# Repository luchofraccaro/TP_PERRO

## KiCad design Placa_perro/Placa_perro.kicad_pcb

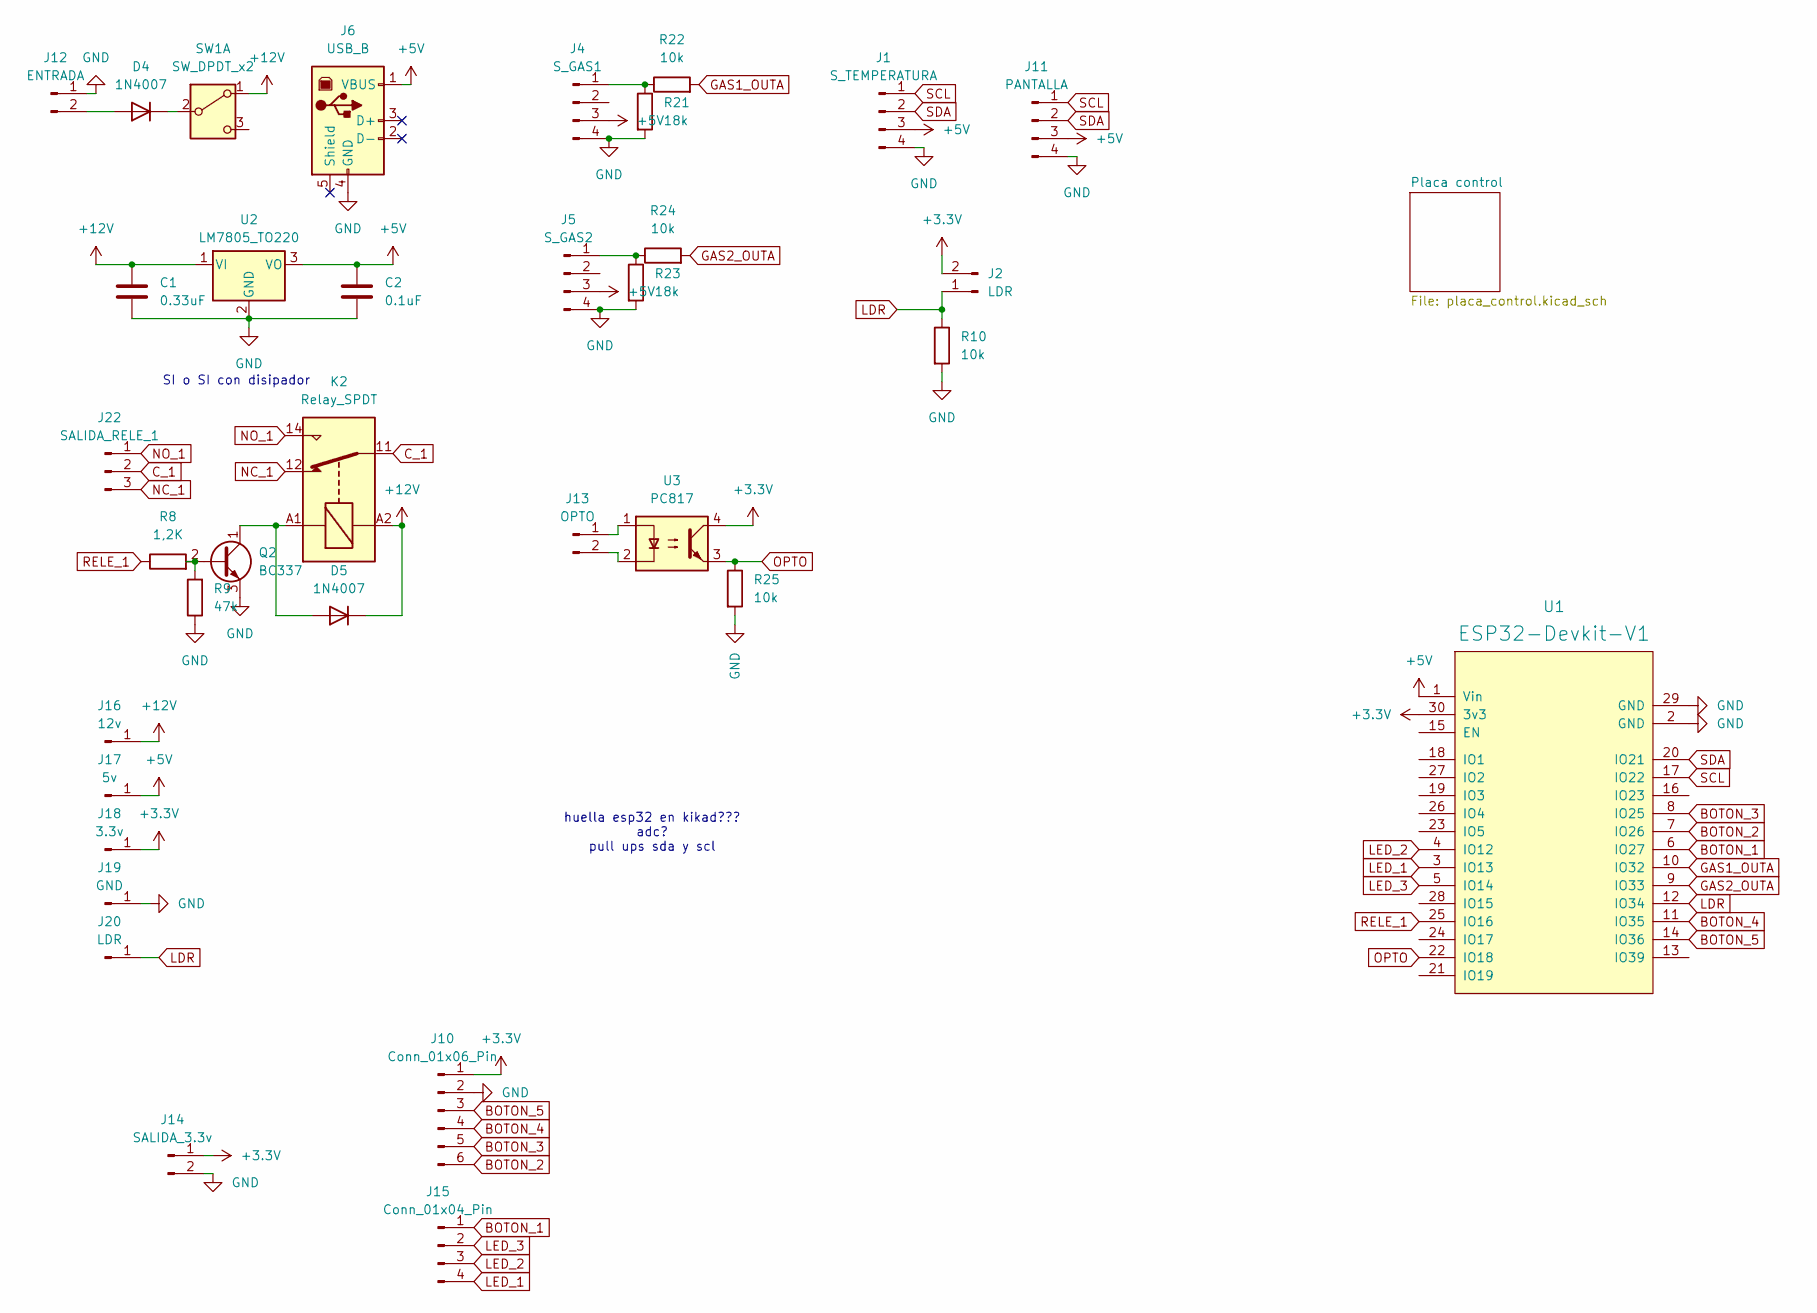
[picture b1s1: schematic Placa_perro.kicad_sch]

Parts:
C1: 0.33uF; C_Disc_D3.8mm_W2.6mm_P2.50mm
C2: 0.1uF; C_Disc_D3.8mm_W2.6mm_P2.50mm
D4, D5: 1N4007; D_DO-41_SOD81_P10.16mm_Horizontal
J1: S_TEMPERATURA; Molex_KK-254_AE-6410-04A_1x04_P2.54mm_Vertical
J2: LDR; Molex_KK-254_AE-6410-02A_1x02_P2.54mm_Vertical
J4: S_GAS1; Molex_KK-254_AE-6410-04A_1x04_P2.54mm_Vertical
J5: S_GAS2; Molex_KK-254_AE-6410-04A_1x04_P2.54mm_Vertical
J6: USB_B; USB_B_Lumberg_2411_02_Horizontal
J10: Conn_01x06_Pin; Molex_KK-254_AE-6410-06A_1x06_P2.54mm_Vertical
J11: PANTALLA; Molex_KK-254_AE-6410-04A_1x04_P2.54mm_Vertical
J12: ENTRADA; TerminalBlock_MaiXu_MX126-5.0-02P_1x02_P5.00mm
J13: OPTO; TerminalBlock_MaiXu_MX126-5.0-02P_1x02_P5.00mm
J14: SALIDA_3.3v; TerminalBlock_MaiXu_MX126-5.0-02P_1x02_P5.00mm
J15: Conn_01x04_Pin; Molex_KK-254_AE-6410-04A_1x04_P2.54mm_Vertical
J16: 12v; PinHeader_1x01_P2.54mm_Vertical
J17: 5v; PinHeader_1x01_P2.54mm_Vertical
J18: 3.3v; PinHeader_1x01_P2.54mm_Vertical
J19: GND; PinHeader_1x01_P2.54mm_Vertical
J20: LDR; PinHeader_1x01_P2.54mm_Vertical
J22: SALIDA_RELE_1; TerminalBlock_MaiXu_MX126-5.0-03P_1x03_P5.00mm
K2: Relay_SPDT; Relay_SPDT_Hongfa_HF3F-L-xx-1ZL1T
Q2: BC337; TO-92_Inline
R8: 1,2K; R_Axial_DIN0207_L6.3mm_D2.5mm_P7.62mm_Horizontal
R9: 47k; R_Axial_DIN0207_L6.3mm_D2.5mm_P7.62mm_Horizontal
R10, R22, R24, R25: 10k; R_Axial_DIN0207_L6.3mm_D2.5mm_P7.62mm_Horizontal
R21, R23: 18k; R_Axial_DIN0207_L6.3mm_D2.5mm_P7.62mm_Horizontal
SW1: SW_DPDT_x2; PinHeader_1x02_P2.54mm_Vertical
U1: ESP32-Devkit-V1; DOIT_ESP32_Devkit_mirko
U2: LM7805_TO220; TO-220-3_Vertical
U3: PC817; DIP-4_W7.62mm

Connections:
+3.3V: J2.2, J10.1, J14.1, J18.1, U1.30 (3v3), U3.4; also elsewhere on the board
+5V: C2.1, J1.3, J4.3, J5.3, J6.1 (VBUS), J11.3, J17.1, U1.1 (Vin), U2.3 (VO)
+12V: C1.1, D5.1 (K), J16.1, K2.A2, SW1.1 (A), U2.1 (VI)
BOTON_1: J15.1, U1.6 (IO27); also elsewhere on the board
BOTON_2: J10.6, U1.7 (IO26); also elsewhere on the board
BOTON_3: J10.5, U1.8 (IO25); also elsewhere on the board
BOTON_4: J10.4, U1.11 (IO35); also elsewhere on the board
BOTON_5: J10.3, U1.14 (IO36); also elsewhere on the board
C_1: J22.2, K2.11
GAS1_OUTA: R22.2, U1.10 (IO32)
GAS2_OUTA: R24.2, U1.9 (IO33)
GND: C1.2, C2.2, J1.4, J4.4, J5.4, J6.4 (GND), J10.2, J11.4, J12.1, J14.2, J19.1, Q2.3 (E), R9.1, R10.2, R21.2, R23.2, R25.2, U1.2 (GND), U1.29 (GND), U2.2 (GND); also elsewhere on the board
LDR: J2.1, J20.1, R10.1, U1.12 (IO34)
LED_1: J15.4, U1.3 (IO13); also elsewhere on the board
LED_2: J15.3, U1.4 (IO12); also elsewhere on the board
LED_3: J15.2, U1.5 (IO14); also elsewhere on the board
NC_1: J22.3, K2.12
NO_1: J22.1, K2.14
unnamed: D4.2 (A), J12.2
unnamed: D4.1 (K), SW1.2 (B)
unnamed: D5.2 (A), K2.A1, Q2.1 (C)
unnamed: J4.1, R21.1, R22.1
unnamed: J5.1, R23.1, R24.1
unnamed: J13.1, U3.1
unnamed: J13.2, U3.2
unnamed: Q2.2 (B), R8.2, R9.2
OPTO: R25.1, U1.22 (IO18), U3.3
RELE_1: R8.1, U1.25 (IO16)
SCL: J1.1, J11.1, U1.17 (IO22)
SDA: J1.2, J11.2, U1.20 (IO21)

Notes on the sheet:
huella esp32 en kikad??? adc? pull ups sda y scl
SI o SI con disipador

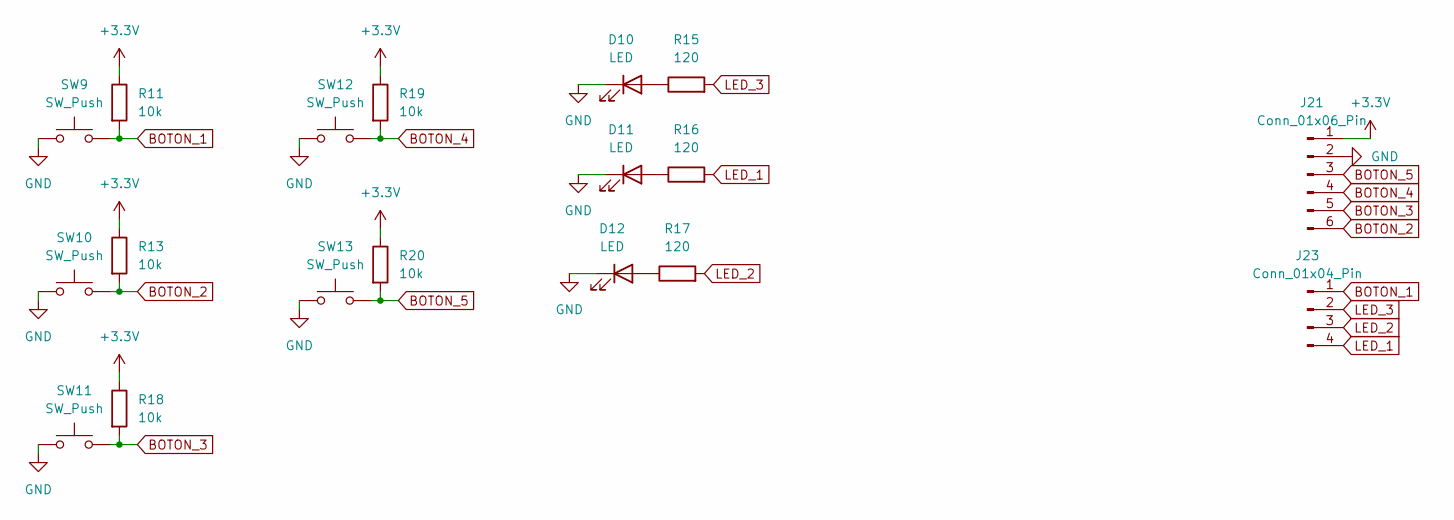
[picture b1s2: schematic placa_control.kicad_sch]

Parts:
D10, D11, D12: LED; LED_D5.0mm
J21: Conn_01x06_Pin; Molex_KK-254_AE-6410-06A_1x06_P2.54mm_Vertical
J23: Conn_01x04_Pin; Molex_KK-254_AE-6410-04A_1x04_P2.54mm_Vertical
R11, R13, R18, R19, R20: 10k; R_Axial_DIN0207_L6.3mm_D2.5mm_P7.62mm_Horizontal
R15, R16, R17: 120; R_Axial_DIN0207_L6.3mm_D2.5mm_P7.62mm_Horizontal
SW9, SW10, SW11, SW12, SW13: SW_Push; SW_PUSH_6mm

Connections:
+3.3V: J21.1, R11.1, R13.1, R18.1, R19.1, R20.1; also elsewhere on the board
BOTON_1: J23.1, R11.2, SW9.2; also elsewhere on the board
BOTON_2: J21.6, R13.2, SW10.2; also elsewhere on the board
BOTON_3: J21.5, R18.2, SW11.2; also elsewhere on the board
BOTON_4: J21.4, R19.2, SW12.2; also elsewhere on the board
BOTON_5: J21.3, R20.2, SW13.2; also elsewhere on the board
GND: D10.1 (K), D11.1 (K), D12.1 (K), J21.2, SW9.1, SW10.1, SW11.1, SW12.1, SW13.1; also elsewhere on the board
LED_1: J23.4, R16.2; also elsewhere on the board
LED_2: J23.3, R17.2; also elsewhere on the board
LED_3: J23.2, R15.2; also elsewhere on the board
unnamed: D10.2 (A), R15.1
unnamed: D11.2 (A), R16.1
unnamed: D12.2 (A), R17.1

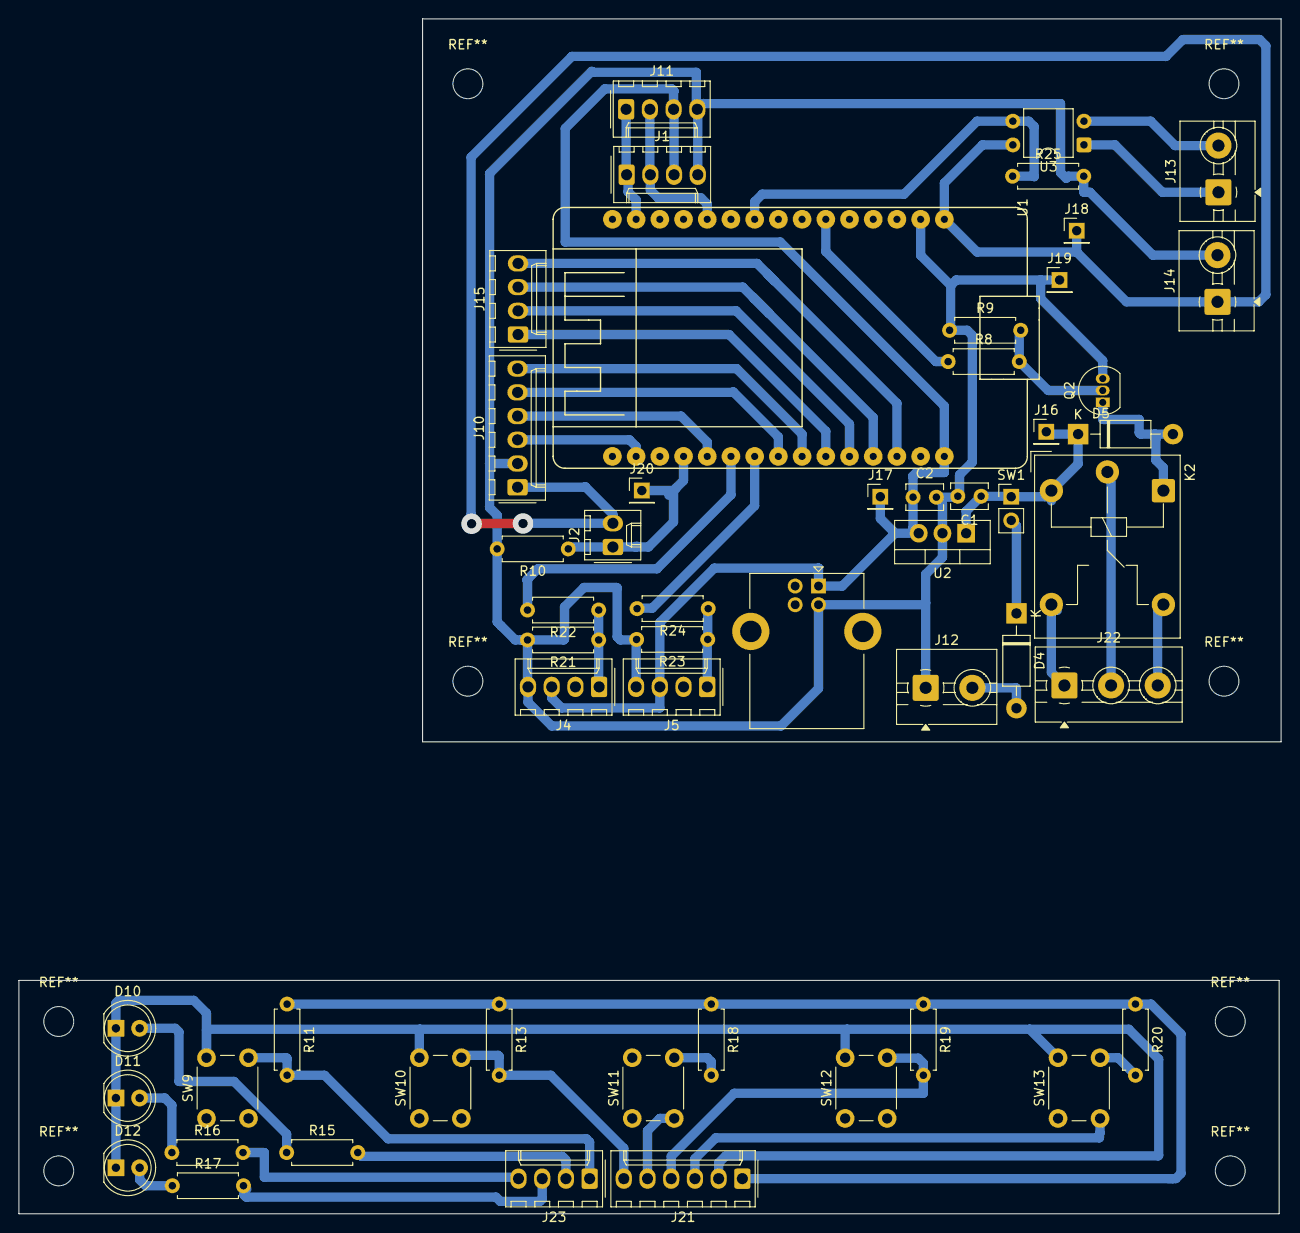
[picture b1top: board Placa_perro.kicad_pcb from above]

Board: 2 copper layers, 135.2 x 128.0 mm, 53 parts (0 on the bottom side), 33 nets.

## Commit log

2025-08-17 primer esquematico
2025-08-22 rutee pcb falta molex
2025-08-25 terminada
